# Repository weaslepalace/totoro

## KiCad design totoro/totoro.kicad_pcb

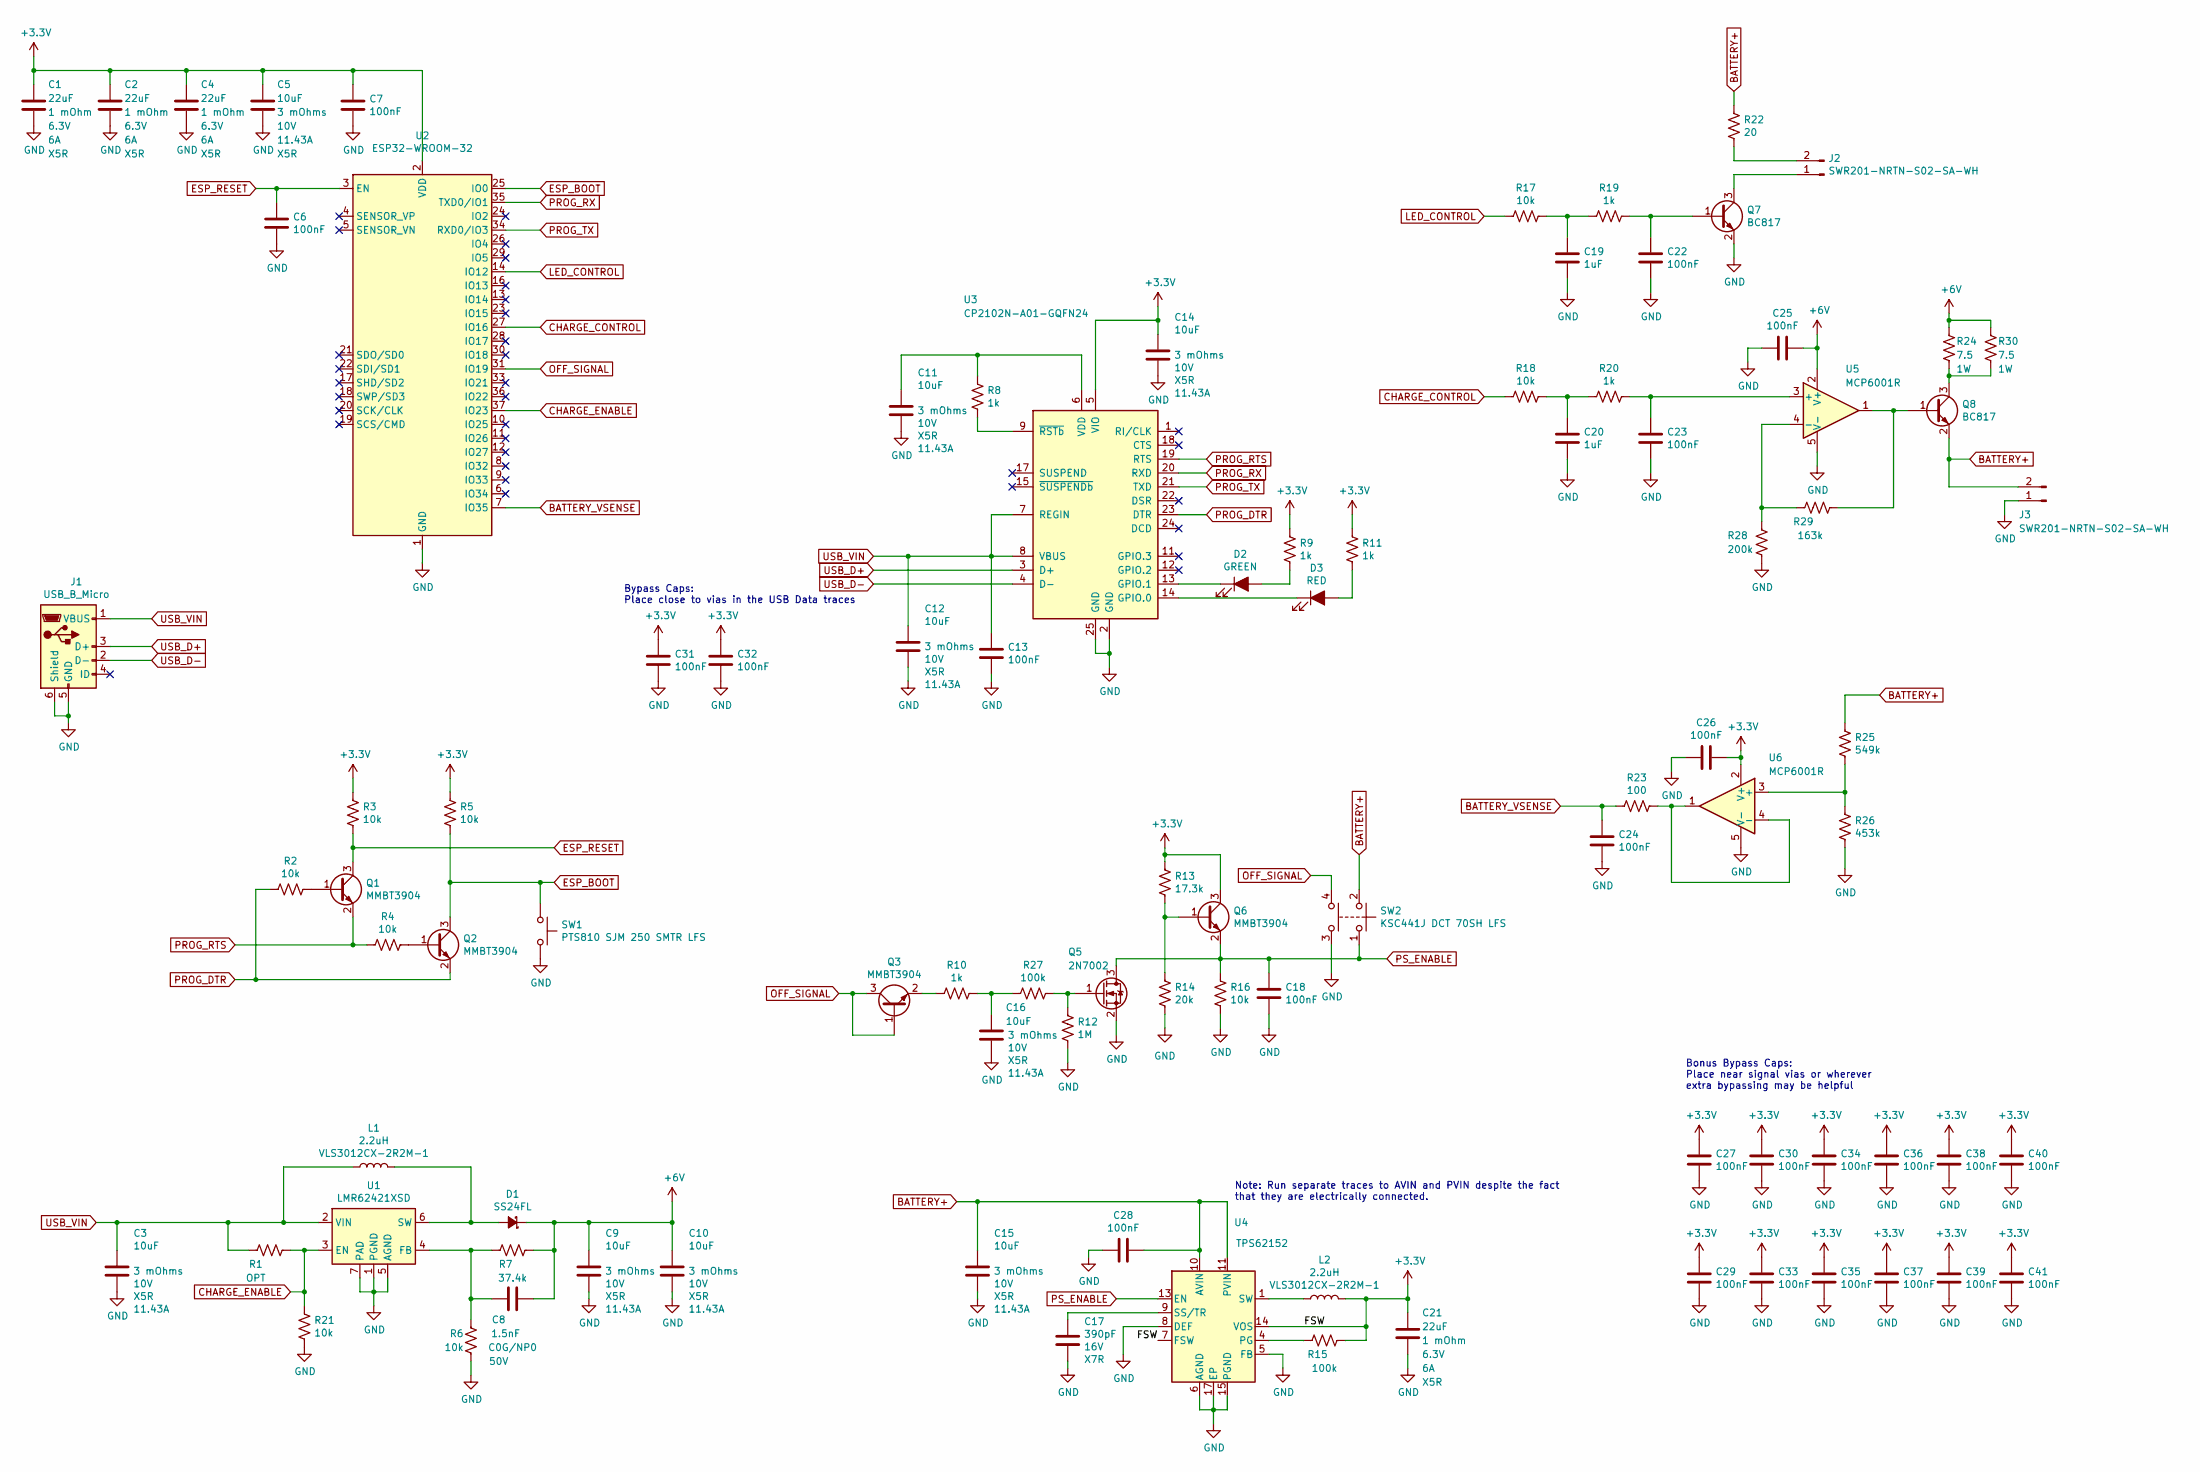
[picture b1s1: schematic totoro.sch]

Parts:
C1, C2, C4, C21: 22uF; C_0805_2012Metric
C3, C5, C9, C10, C11, C12, C14, C15, C16: 10uF; C_0805_2012Metric
C6, C7, C13, C18, C22, C23, C24, C25, C26, C27, C28, C29, C30, C33, C34, C35, C36, C37, C38, C39, C40, C41: 100nF; C_0603_1608Metric
C8: 1.5nF; C_0603_1608Metric
C17: 390pF; C_0603_1608Metric
C19, C20: 1uF; C_0603_1608Metric
C31, C32: 100nF; C_0603_1608Metric_Pad1.05x0.95mm_HandSolder
D1: SS24FL; D_SOD-123F
D2: GREEN; LED_0603_1608Metric
D3: RED; LED_0603_1608Metric
J1: USB_B_Micro; USB_Micro-B_Amphenol_10103594-0001LF_Horizontal
J2, J3: SWR201-NRTN-S02-SA-WH; SWR201
L1, L2: 2.2uH; VLS3012CX-1; PartNumber VLS3012CX-2R2M-1
Q1, Q2, Q3, Q6: MMBT3904; SOT-23
Q5: 2N7002; SOT-23
Q7, Q8: BC817; SOT-23
R1: OPT; R_0603_1608Metric
R2, R3, R4, R5, R6, R16, R17, R18, R21: 10k; R_0603_1608Metric
R7: 37.4k; R_0603_1608Metric
R8, R9, R11, R19, R20: 1k; R_0603_1608Metric
R10: 1k; R_0603_1608Metric_Pad1.05x0.95mm_HandSolder
R12: 1M; R_0603_1608Metric
R13: 17.3k; R_0603_1608Metric
R14: 20k; R_0603_1608Metric
R15: 100k; R_0603_1608Metric
R22: 20; R_0603_1608Metric
R23: 100; R_0603_1608Metric
R24, R30: 7.5; R_2512_6332Metric
R25: 549k; R_0603_1608Metric
R26: 453k; R_0603_1608Metric
R27: 100k; R_0603_1608Metric_Pad1.05x0.95mm_HandSolder
R28: 200k; R_0603_1608Metric
R29: 163k; R_0603_1608Metric
SW1: PTS810 SJM 250 SMTR LFS; SW_SPST_PTS810
SW2: KSC441J DCT 70SH LFS; KSC441J
U1: LMR62421XSD; WSON-6-1EP_3x3mm_P0.95mm
U2: ESP32-WROOM-32
U3: CP2102N-A01-GQFN24; QFN-24-1EP_4x4mm_P0.5mm_EP2.6x2.6mm
U4: TPS62152; VQFN-16-1EP_3x3mm_P0.5mm_EP1.68x1.68mm_ThermalVias
U5, U6: MCP6001R; SOT-23-5

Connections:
+3V3: C1.1, C2.1, C4.1, C5.1, C7.1, C14.1, C21.1, C26.1, C27.1, C29.1, C30.1, C31.1, C32.1, C33.1, C34.1, C35.1, C36.1, C37.1, C38.1, C39.1, C40.1, C41.1, L2.2, Q6.3 (C), R3.1, R5.1, R9.1, R11.1, R13.2, R15.1, U2.2 (VDD), U3.5 (VIO), U4.7 (FSW), U4.14 (VOS), U6.2 (V+)
+6V: C8.2, C9.1, C10.1, C25.1, D1.1 (K), R7.1, R24.1, R30.1, U5.2 (V+)
BATTERY+: C15.1, C28.1, J3.2, Q8.2 (E), R22.1, R25.1, SW2.2, U4.10 (AVIN), U4.11 (PVIN), U4.12 (PVIN)
BATTERY_VSENSE: C24.1, R23.2, U2.7 (IO35)
CHARGE_CONTROL: R18.2, U2.27 (IO16)
CHARGE_ENABLE: R1.2, R21.1, U1.3 (EN), U2.37 (IO23)
ESP_BOOT: Q2.3 (C), R5.2, SW1.1, U2.25 (IO0)
ESP_RESET: C6.1, Q1.3 (C), R3.2, U2.3 (EN)
GND: C1.2, C2.2, C3.2, C4.2, C5.2, C6.2, C7.2, C9.2, C10.2, C11.2, C12.2, C13.2, C14.2, C15.2, C16.2, C17.2, C18.2, C19.2, C20.2, C21.2, C22.2, C23.2, C24.2, C25.2, C26.2, C27.2, C28.2, C29.2, C30.2, C31.2, C32.2, C33.2, C34.2, C35.2, C36.2, C37.2, C38.2, C39.2, C40.2, C41.2, J1.5 (GND), J1.6 (Shield), J3.1, Q5.2 (S), Q7.2 (E), R6.2, R12.2, R14.2, R16.2, R21.2, R26.2, R28.2, SW1.2, SW2.3, U1.1 (PGND), U1.5 (AGND), U1.7 (PAD), U2.1 (GND), U2.15 (GND), U2.38 (GND), U2.39, U3.2 (GND), U3.25 (GND), U4.5 (FB), U4.6 (AGND), U4.8 (DEF), U4.15 (PGND), U4.16 (PGND), U4.17 (EP), U5.5 (V-), U6.5 (V-)
LED_CONTROL: R17.2, U2.14 (IO12)
unnamed: C8.1, R6.1, R7.2, U1.4 (FB)
unnamed: C11.1, R8.1, U3.6 (VDD)
unnamed: C16.1, R10.1, R27.2
unnamed: C17.1, U4.9 (SS/TR)
unnamed: C19.1, R17.1, R19.2
unnamed: C20.1, R18.1, R20.2
unnamed: C22.1, Q7.1 (B), R19.1
unnamed: C23.1, R20.1, U5.3 (+)
unnamed: D1.2 (A), L1.2, U1.6 (SW)
unnamed: D2.1 (K), U3.13 (GPIO.1)
unnamed: D2.2 (A), R9.2
unnamed: D3.1 (K), U3.14 (GPIO.0)
unnamed: D3.2 (A), R11.2
unnamed: J2.1, Q7.3 (C)
unnamed: J2.2, R22.2
unnamed: L2.1, U4.1 (SW), U4.2 (SW), U4.3 (SW)
unnamed: Q1.1 (B), R2.1
unnamed: Q2.1 (B), R4.1
unnamed: Q3.2 (E), R10.2
unnamed: Q5.1 (G), R12.1, R27.1
unnamed: Q6.1 (B), R13.1, R14.1
unnamed: Q8.1 (B), R29.1, U5.1
unnamed: Q8.3 (C), R24.2, R30.2
unnamed: R8.2, U3.9 (~RSTb)
unnamed: R15.2, U4.4 (PG)
unnamed: R23.1, U6.1, U6.4 (-)
unnamed: R25.2, R26.1, U6.3 (+)
unnamed: R28.1, R29.2, U5.4 (-)
OFF_SIGNAL: Q3.1 (B), Q3.3 (C), SW2.4, U2.31 (IO19)
PROG_DTR: Q2.2 (E), R2.2, U3.23 (DTR)
PROG_RTS: Q1.2 (E), R4.2, U3.19 (RTS)
PROG_RX: U2.35 (TXD0/IO1), U3.20 (RXD)
PROG_TX: U2.34 (RXD0/IO3), U3.21 (TXD)
PS_ENABLE: C18.1, Q5.3 (D), Q6.2 (E), R16.1, SW2.1, U4.13 (EN)
USB_D+: J1.3 (D+), U3.3 (D+)
USB_D-: J1.2 (D-), U3.4 (D-)
USB_VIN: C3.1, C12.1, C13.1, J1.1 (VBUS), L1.1, R1.1, U1.2 (VIN), U3.7 (REGIN), U3.8 (VBUS)

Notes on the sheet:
Note: Run separate traces to AVIN and PVIN despite the fact that they are electrically connected.
Bypass Caps: Place close to vias in the USB Data traces
Bonus Bypass Caps: Place near signal vias or wherever extra bypassing may be helpful

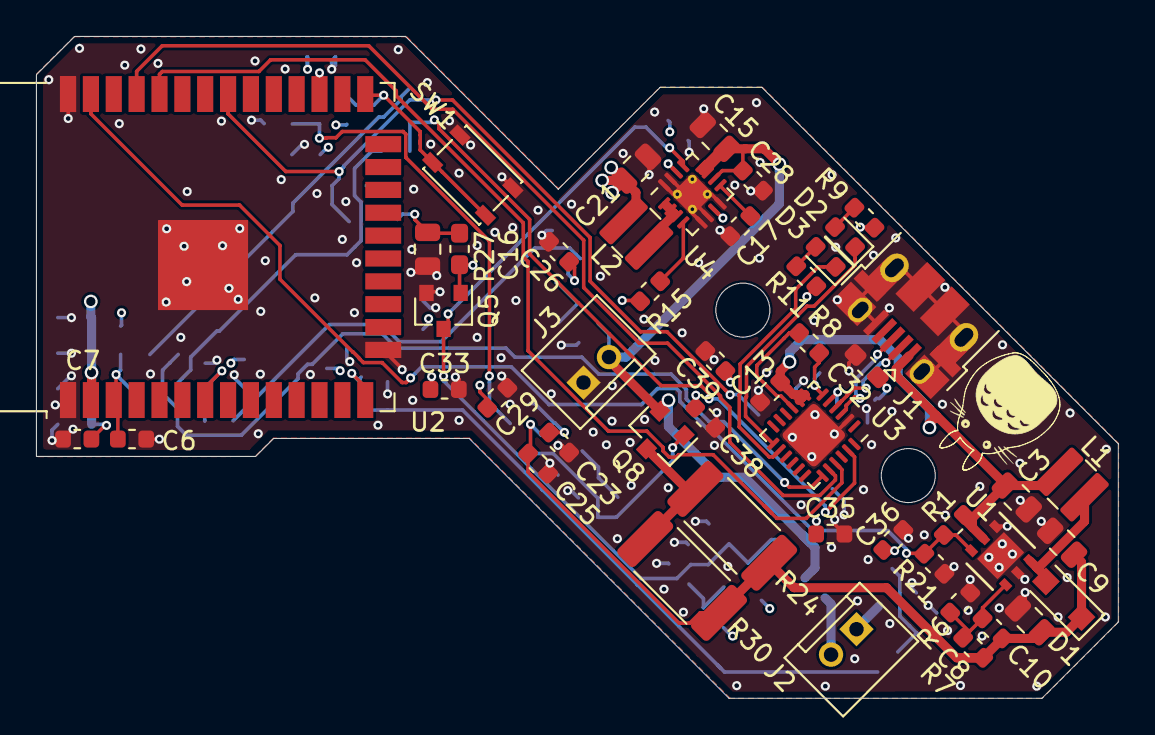
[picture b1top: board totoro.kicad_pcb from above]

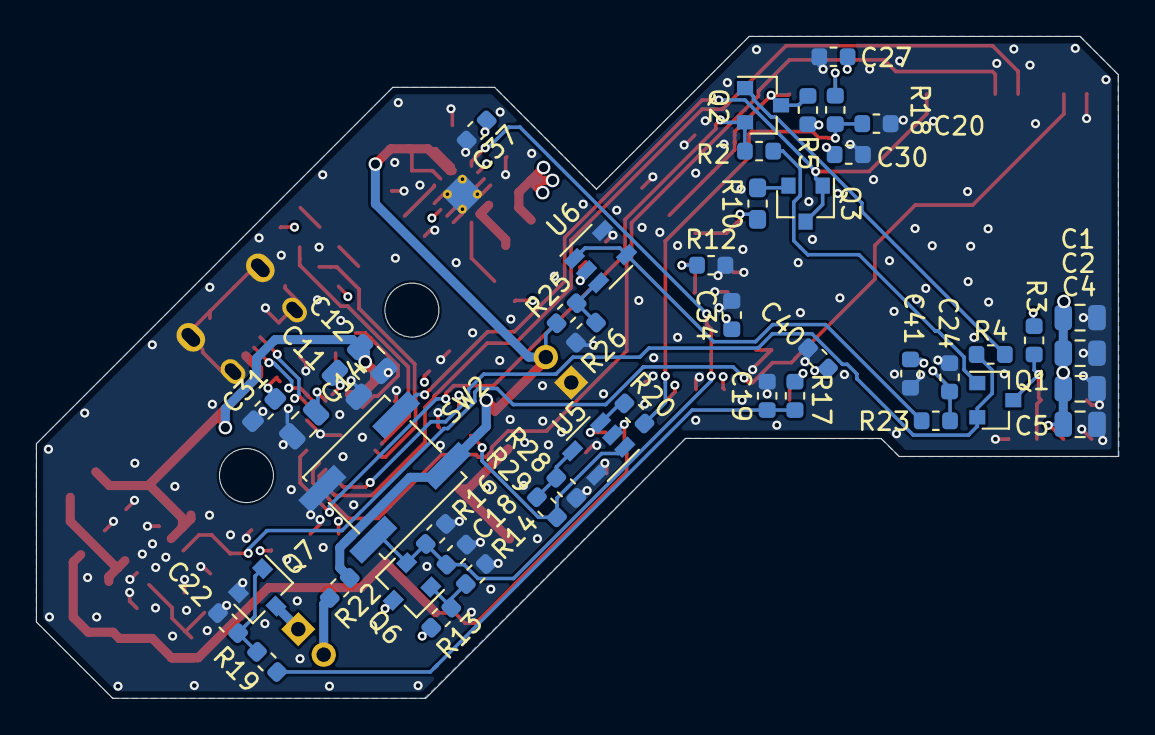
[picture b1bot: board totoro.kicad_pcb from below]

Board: 4 copper layers, 60.1 x 36.8 mm, 94 parts (46 on the bottom side), 47 nets.

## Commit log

2019-07-21 Starting placement
2019-07-22 All parts are in the circle
2019-07-28 Drew board tentative outline
2019-07-28 Routed some traces. Shrunk board outline.
2019-07-29 Poured copper and stitched with vias
2019-07-29 Added totoro image to silkscreen
2019-07-30 Silkscreen beautified
2019-07-31 DRC clean
2019-07-31 Replaced mounting holes with actual mounting holes
2019-08-08 Outline modification to improve fit. Ordered on OSHPark.
2020-04-04 Created BOM, minor value changes
2020-04-04 Oops, forgot to save
